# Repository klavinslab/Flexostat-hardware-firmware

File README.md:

# The project has moved to it's own [github page](https://github.com/flexostat ).

Please visit https://github.com/flexostat for the latest designs.

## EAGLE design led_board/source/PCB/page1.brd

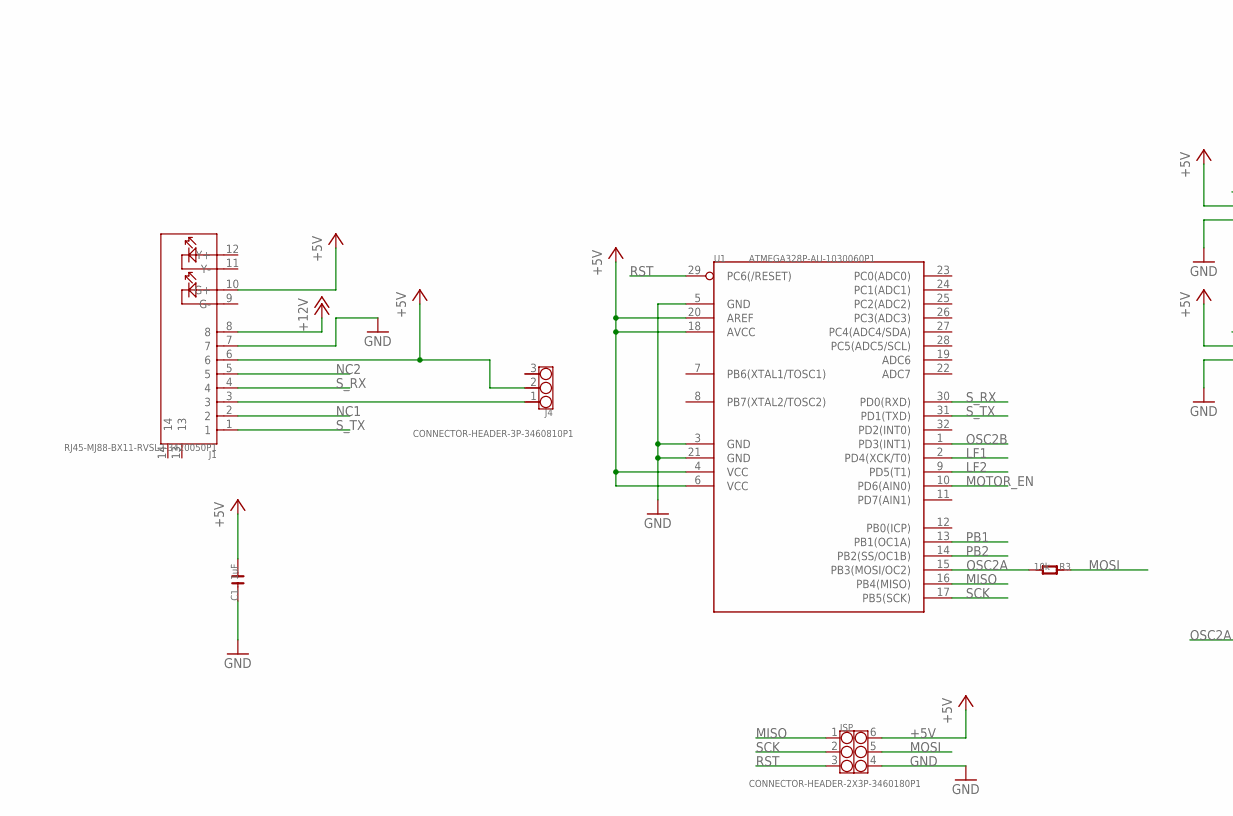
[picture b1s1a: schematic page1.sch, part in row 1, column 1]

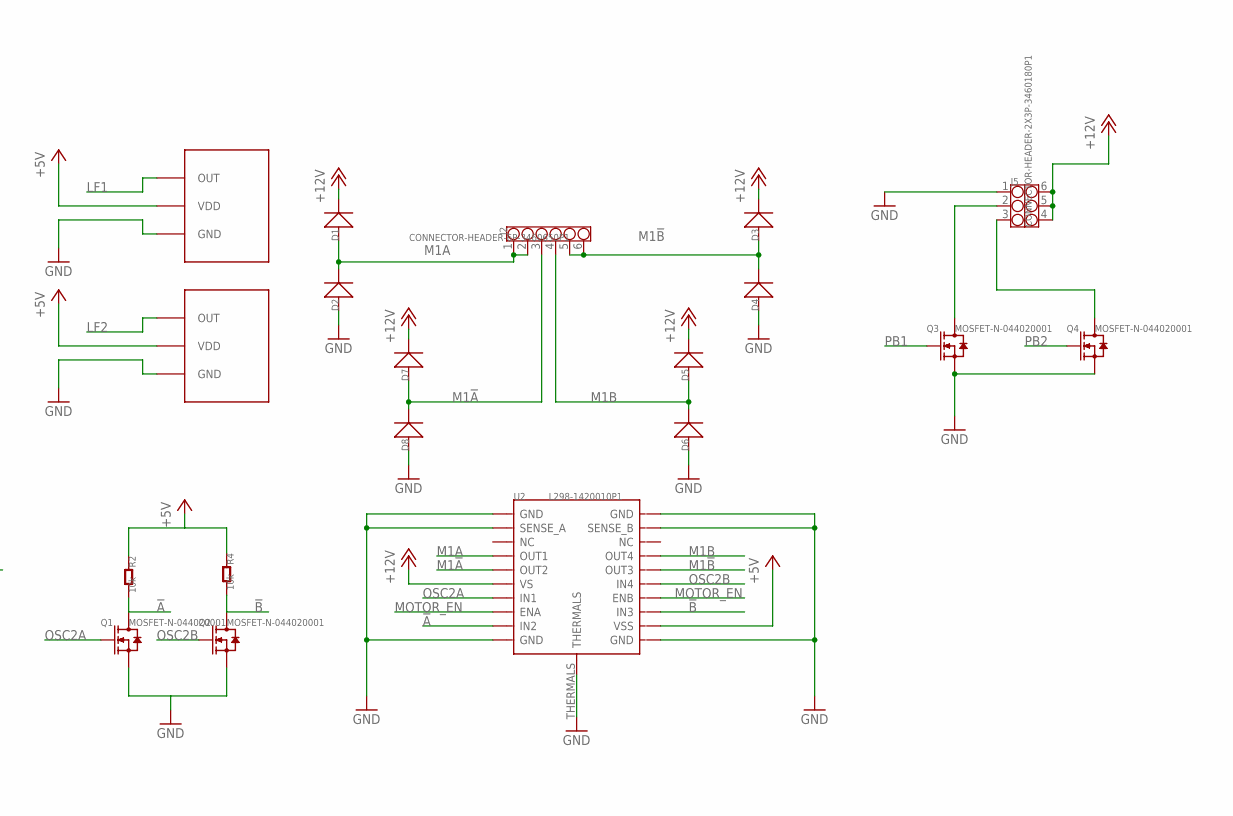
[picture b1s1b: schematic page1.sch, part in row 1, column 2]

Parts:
C1: 1uF; C0805
D1, D2, D3, D4, D5, D6, D7, D8: D-SMA; DO-214AC
ISP: CONNECTOR-HEADER-2X3P-3460180P1; 2X3P-2.54-2.54-11.6-3.0-BLACK-MALE
J1: RJ45-MJ88-BX11-RVSL2-3420050P1; RJ45-MJ88-BX11-RVSL2
J2: CONNECTOR-HEADER-6P-3460650P1; 1X6P-2.54-2.54-11.6-3.0-BLACK-MALE
J4: CONNECTOR-HEADER-3P-3460810P1; 1X3P-2.54-2.54-11.6-3.0-BLACK-MALE
J5: CONNECTOR-HEADER-2X3P-3460180P1; 2X3P-2.54-2.54-11.6-3.0-BLACK-MALE
Q1, Q2, Q3, Q4: MOSFET-N-044020001; SOT23
R2, R3, R4: 10k; R0603
U1: ATMEGA328P-AU-1030060P1; TQFP32
U2: L298-1420010P1; POWERSO-20
U$5, U$6: TSL235; TSL235R-2MM-S

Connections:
!A: Q1.3 (D), R2.2, U2.9 (IN2)
!B: Q2.3 (D), R4.2, U2.13 (IN3)
+5V: C1.2, ISP.6, J1.6, J1.10 (G+), J4.2, R2.1, R4.1, U1.4 (VCC), U1.6 (VCC), U1.18 (AVCC), U1.20 (AREF), U2.12 (VSS), U$5.P$2 (VDD), U$6.P$2 (VDD)
+12V: D1.2 (-), D3.2 (-), D5.2 (-), D7.2 (-), J1.8, J5.4, J5.5, J5.6, U2.6 (VS)
GND: C1.1, D2.1 (+), D4.1 (+), D6.1 (+), D8.1 (+), ISP.4, J1.7, J5.1, Q1.2 (S), Q2.2 (S), Q3.2 (S), Q4.2 (S), U1.3 (GND), U1.5 (GND), U1.21 (GND), U2.1 (GND), U2.2 (SENSE_A), U2.10 (GND), U2.11 (GND), U2.19 (SENSE_B), U2.20 (GND), U2.THERMALS, U$5.P$1 (GND), U$6.P$1 (GND)
LF1: U1.2 (PD4(XCK/T0)), U$5.P$3 (OUT)
LF2: U1.9 (PD5(T1)), U$6.P$3 (OUT)
M1!A: D7.1 (+), D8.2 (-), J2.3, U2.5 (OUT2)
M1!B: D3.1 (+), D4.2 (-), J2.5, J2.6, U2.16 (OUT3)
M1A: D1.1 (+), D2.2 (-), J2.1, J2.2, U2.4 (OUT1)
M1B: D5.1 (+), D6.2 (-), J2.4, U2.17 (OUT4)
MISO: ISP.1, U1.16 (PB4(MISO))
MOSI: ISP.5, R3.1
MOTOR_EN: U1.10 (PD6(AIN0)), U2.8 (ENA), U2.14 (ENB)
unnamed: J1.3, J4.1
unnamed: J5.3, Q4.3 (D)
unnamed: J5.2, Q3.3 (D)
NC1: J1.2
NC2: J1.5
OSC2A: Q1.1 (G), R3.2, U1.15 (PB3(MOSI/OC2)), U2.7 (IN1)
OSC2B: Q2.1 (G), U1.1 (PD3(INT1)), U2.15 (IN4)
PB1: Q3.1 (G), U1.13 (PB1(OC1A))
PB2: Q4.1 (G), U1.14 (PB2(SS/OC1B))
RST: ISP.3, U1.29 (PC6(/RESET))
SCK: ISP.2, U1.17 (PB5(SCK))
S_RX: J1.4, U1.30 (PD0(RXD))
S_TX: J1.1, U1.31 (PD1(TXD))

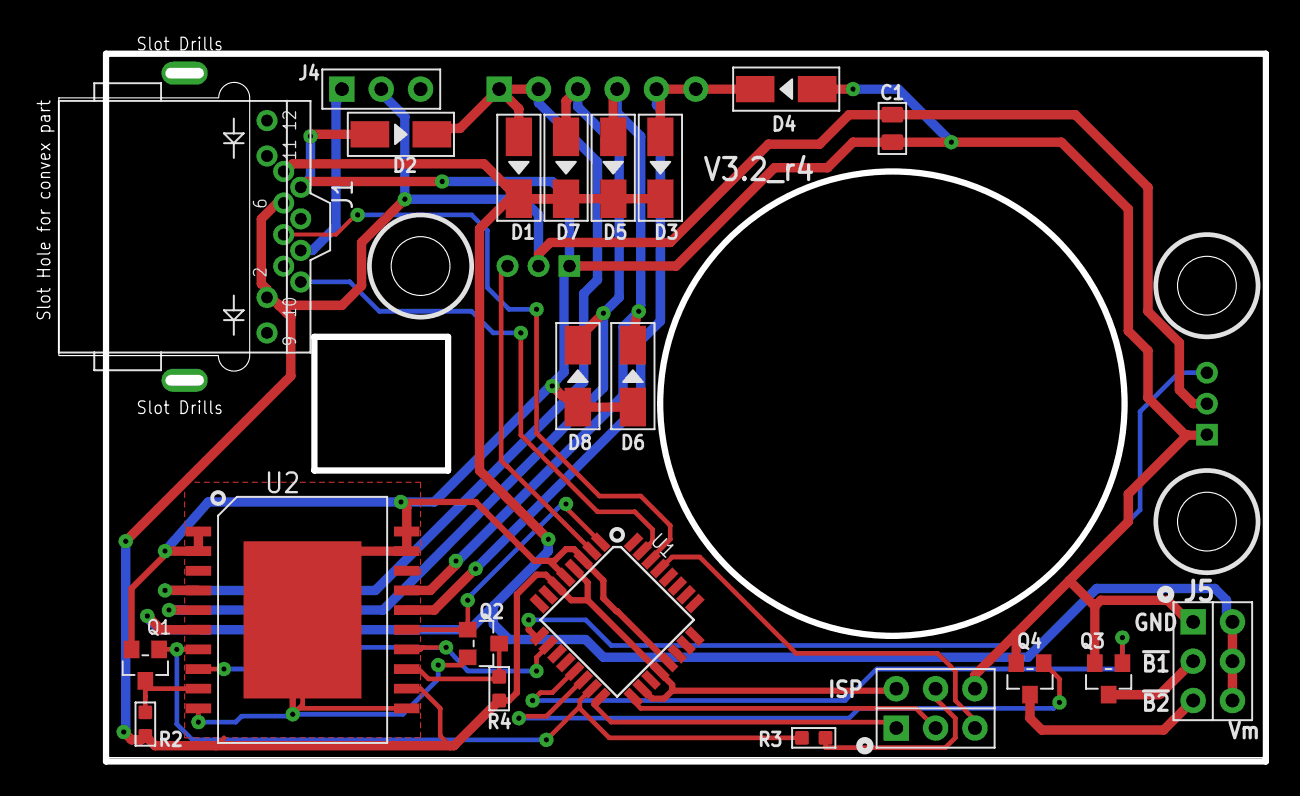
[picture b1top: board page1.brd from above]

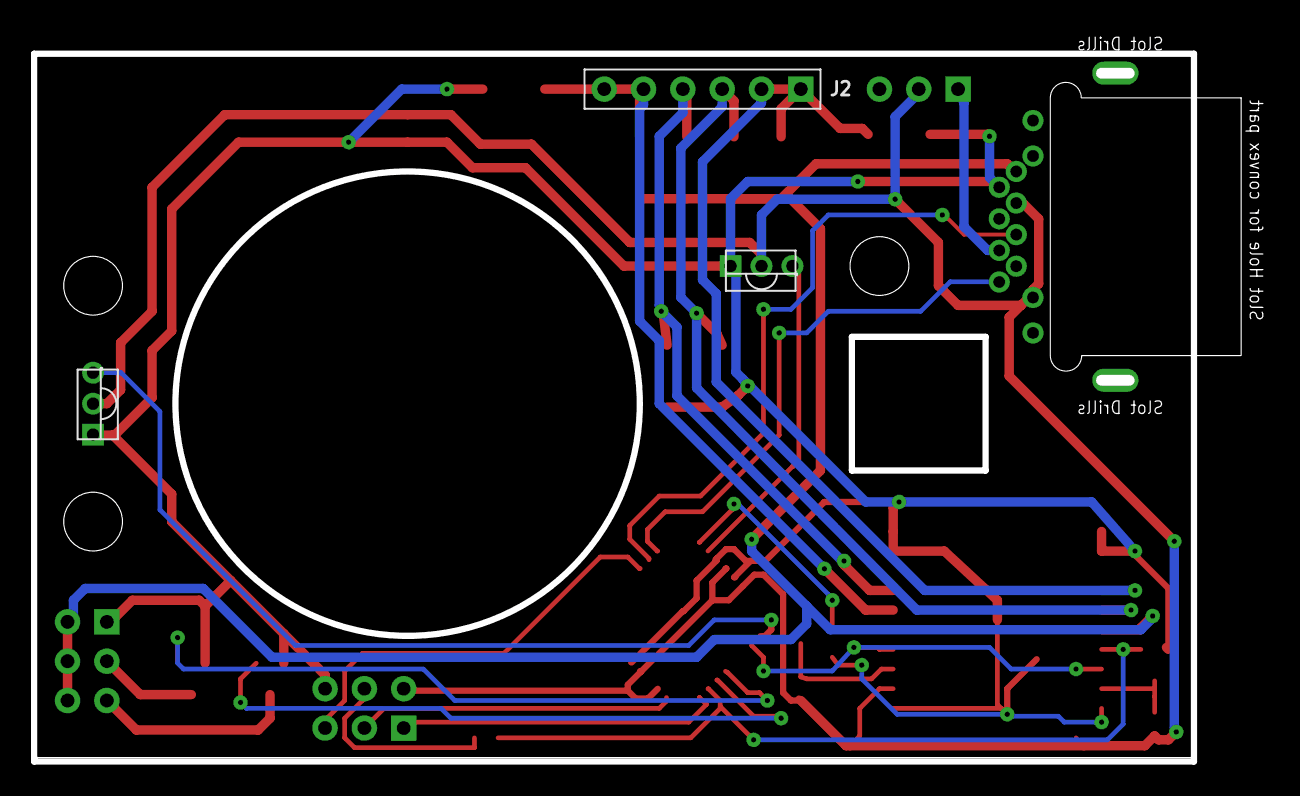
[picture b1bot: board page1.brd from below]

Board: 4 copper layers, 79.3 x 46.7 mm, 25 parts (3 on the bottom side), 25 nets.

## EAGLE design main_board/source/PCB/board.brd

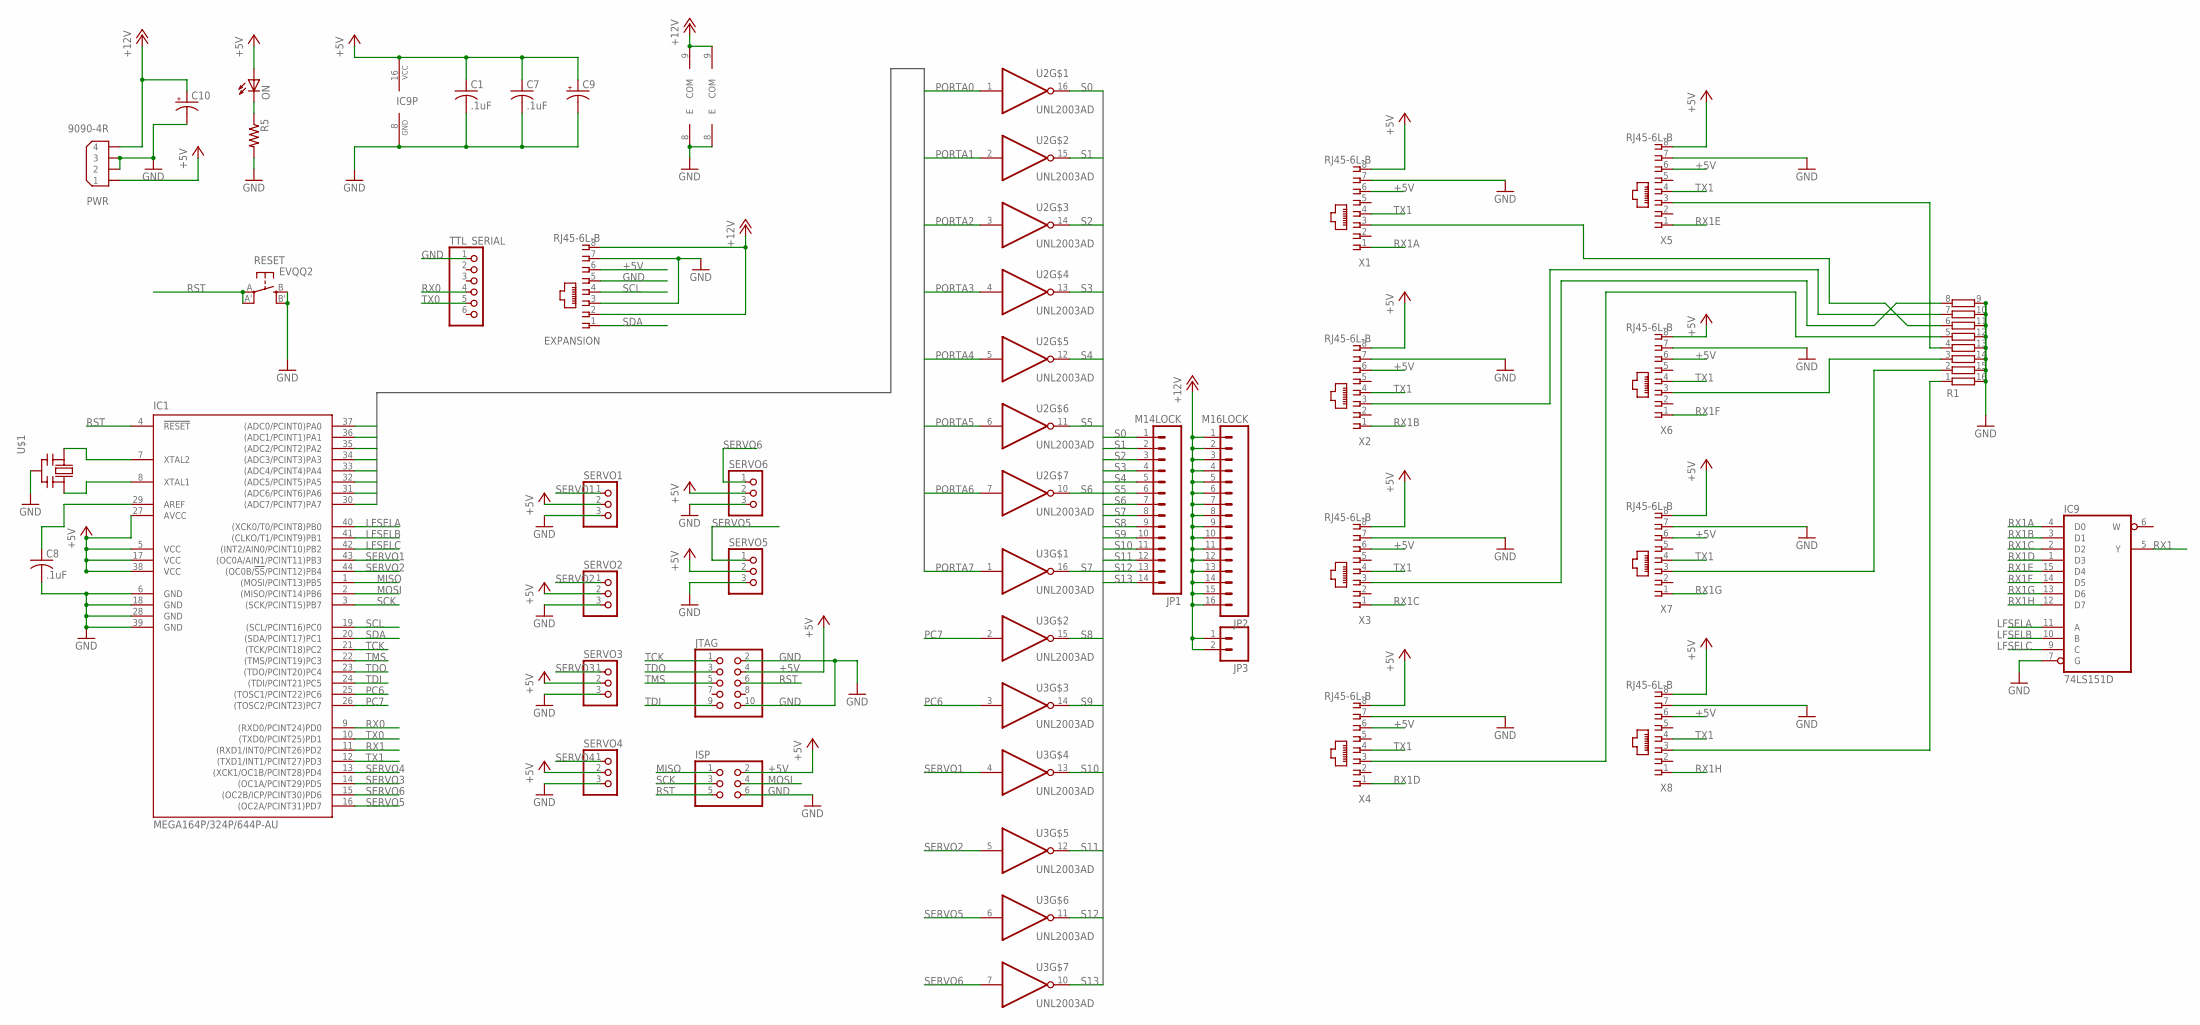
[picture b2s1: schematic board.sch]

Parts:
C1, C7, C8: .1uF; C0805
C9, C10: CPOL-USE2.5-7; E2,5-7
EXPANSION: RJ45-6L-B; RJ45-NO-SHIELD
IC1: MEGA164P/324P/644P-AU; TQFP44
IC9: 74LS151D; SO16
ISP: PINHD-2X3; 2X03
JP1: M14LOCK; 1X14_LOCK
JP2: M16LOCK; 1X16_LOCK
JP3: M02PTH; 1X02
JTAG: PINHD-2X5; 2X05
ON: LEDCHIPLED_0805; CHIPLED_0805
PWR: 9090-4R
R1: 2NBS16-8; SO16
R5: R-US_R0805; R0805
RESET: EVQQ2; EVQ-Q2
SERVO1, SERVO2, SERVO3, SERVO4, SERVO5, SERVO6: PINHD-1X3; 1X03
TTL_SERIAL: PINHD-1X6; 1X06
U2, U3: UNL2003AD; SO16
U$1: CERMOSCILL-CSTCRG; CSTCR-G
X1, X2, X3, X4, X5, X6, X7, X8: RJ45-6L-B; RJ45-NO-SHIELD

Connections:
+5V: C1.1, C7.1, C9.+, EXPANSION.6, IC1.5 (VCC), IC1.17 (VCC), IC1.27 (AVCC), IC1.38 (VCC), IC9.16 (VCC), ISP.2, JTAG.4, ON.A, PWR.1, SERVO1.2, SERVO2.2, SERVO3.2, SERVO4.2, SERVO5.2, SERVO6.2, X1.6, X1.8, X2.6, X2.8, X3.6, X3.8, X4.6, X4.8, X5.6, X5.8, X6.6, X6.8, X7.6, X7.8, X8.6, X8.8
+12V: C10.+, EXPANSION.2, EXPANSION.8, JP2.1, JP2.2, JP2.3, JP2.4, JP2.5, JP2.6, JP2.7, JP2.8, JP2.9, JP2.10, JP2.11, JP2.12, JP2.13, JP2.14, JP2.15, JP2.16, JP3.1, JP3.2, PWR.4, U2.9 (COM), U3.9 (COM)
GND: C1.2, C7.2, C8.2, C9.-, C10.-, EXPANSION.3, EXPANSION.5, EXPANSION.7, IC1.6 (GND), IC1.18 (GND), IC1.28 (GND), IC1.39 (GND), IC9.7 (G), IC9.8 (GND), ISP.6, JTAG.2, JTAG.10, PWR.2, PWR.3, R1.9, R1.10, R1.11, R1.12, R1.13, R1.14, R1.15, R1.16, R5.2, RESET.B (S), RESET.B' (S1), SERVO1.3, SERVO2.3, SERVO3.3, SERVO4.3, SERVO5.3, SERVO6.3, TTL_SERIAL.1, U2.8 (E), U3.8 (E), U$1.2 (GND), X1.7, X2.7, X3.7, X4.7, X5.7, X6.7, X7.7, X8.7
LFSELA: IC1.40 ((XCK0/T0/PCINT8)PB0), IC9.11 (A)
LFSELB: IC1.41 ((CLKO/T1/PCINT9)PB1), IC9.10 (B)
LFSELC: IC1.42 ((INT2/AIN0/PCINT10)PB2), IC9.9 (C)
MISO: IC1.1 ((MOSI/PCINT13)PB5), ISP.1
MOSI: IC1.2 ((MISO/PCINT14)PB6), ISP.4
unnamed: IC1.7 (XTAL2), U$1.1 (IN)
unnamed: IC1.8 (XTAL1), U$1.3 (OUT)
unnamed: R1.1, X8.3
unnamed: R1.6, X1.3
unnamed: R1.7, X2.3
unnamed: R1.8, X3.3
unnamed: R1.5, X4.3
unnamed: R1.4, X5.3
unnamed: R1.3, X6.3
unnamed: R1.2, X7.3
unnamed: C8.1, IC1.29 (AREF)
unnamed: ON.C, R5.1
PC6: IC1.25 ((TOSC1/PCINT22)PC6), U3.3 (I)
PC7: IC1.26 ((TOSC2/PCINT23)PC7), U3.2 (I)
PORTA0: IC1.37 ((ADC0/PCINT0)PA0), U2.1 (I)
PORTA1: IC1.36 ((ADC1/PCINT1)PA1), U2.2 (I)
PORTA2: IC1.35 ((ADC2/PCINT2)PA2), U2.3 (I)
PORTA3: IC1.34 ((ADC3/PCINT3)PA3), U2.4 (I)
PORTA4: IC1.33 ((ADC4/PCINT4)PA4), U2.5 (I)
PORTA5: IC1.32 ((ADC5/PCINT5)PA5), U2.6 (I)
PORTA6: IC1.31 ((ADC6/PCINT6)PA6), U2.7 (I)
PORTA7: IC1.30 ((ADC7/PCINT7)PA7), U3.1 (I)
RST: IC1.4 (!RESET), ISP.5, JTAG.6, RESET.A, RESET.A' (P1)
RX0: IC1.9 ((RXD0/PCINT24)PD0), TTL_SERIAL.4
RX1: IC1.11 ((RXD1/INT0/PCINT26)PD2), IC9.5 (Y)
RX1A: IC9.4 (D0), X1.1
RX1B: IC9.3 (D1), X2.1
RX1C: IC9.2 (D2), X3.1
RX1D: IC9.1 (D3), X4.1
RX1E: IC9.15 (D4), X5.1
RX1F: IC9.14 (D5), X6.1
RX1G: IC9.13 (D6), X7.1
RX1H: IC9.12 (D7), X8.1
S0: JP1.1, U2.16 (O)
S1: JP1.2, U2.15 (O)
S2: JP1.3, U2.14 (O)
S3: JP1.4, U2.13 (O)
S4: JP1.5, U2.12 (O)
S5: JP1.6, U2.11 (O)
S6: JP1.7, U2.10 (O)
S7: JP1.8, U3.16 (O)
S8: JP1.9, U3.15 (O)
S9: JP1.10, U3.14 (O)
S10: JP1.11, U3.13 (O)
S11: JP1.12, U3.12 (O)
S12: JP1.13, U3.11 (O)
S13: JP1.14, U3.10 (O)
SCK: IC1.3 ((SCK/PCINT15)PB7), ISP.3
SCL: EXPANSION.4, IC1.19 ((SCL/PCINT16)PC0)
SDA: EXPANSION.1, IC1.20 ((SDA/PCINT17)PC1)
SERVO1: IC1.43 ((OC0A/AIN1/PCINT11)PB3), SERVO1.1, U3.4 (I)
SERVO2: IC1.44 ((OC0B/!SS!/PCINT12)PB4), SERVO2.1, U3.5 (I)
SERVO3: IC1.14 ((OC1A/PCINT29)PD5), SERVO3.1
SERVO4: IC1.13 ((XCK1/OC1B/PCINT28)PD4), SERVO4.1
SERVO5: IC1.16 ((OC2A/PCINT31)PD7), SERVO5.1, U3.6 (I)
SERVO6: IC1.15 ((OC2B/ICP/PCINT30)PD6), SERVO6.1, U3.7 (I)
TCK: IC1.21 ((TCK/PCINT18)PC2), JTAG.1
TDI: IC1.24 ((TDI/PCINT21)PC5), JTAG.9
TDO: IC1.23 ((TDO/PCINT20)PC4), JTAG.3
TMS: IC1.22 ((TMS/PCINT19)PC3), JTAG.5
TX0: IC1.10 ((TXD0/PCINT25)PD1), TTL_SERIAL.5
TX1: IC1.12 ((TXD1/INT1/PCINT27)PD3), X1.4, X2.4, X3.4, X4.4, X5.4, X6.4, X7.4, X8.4

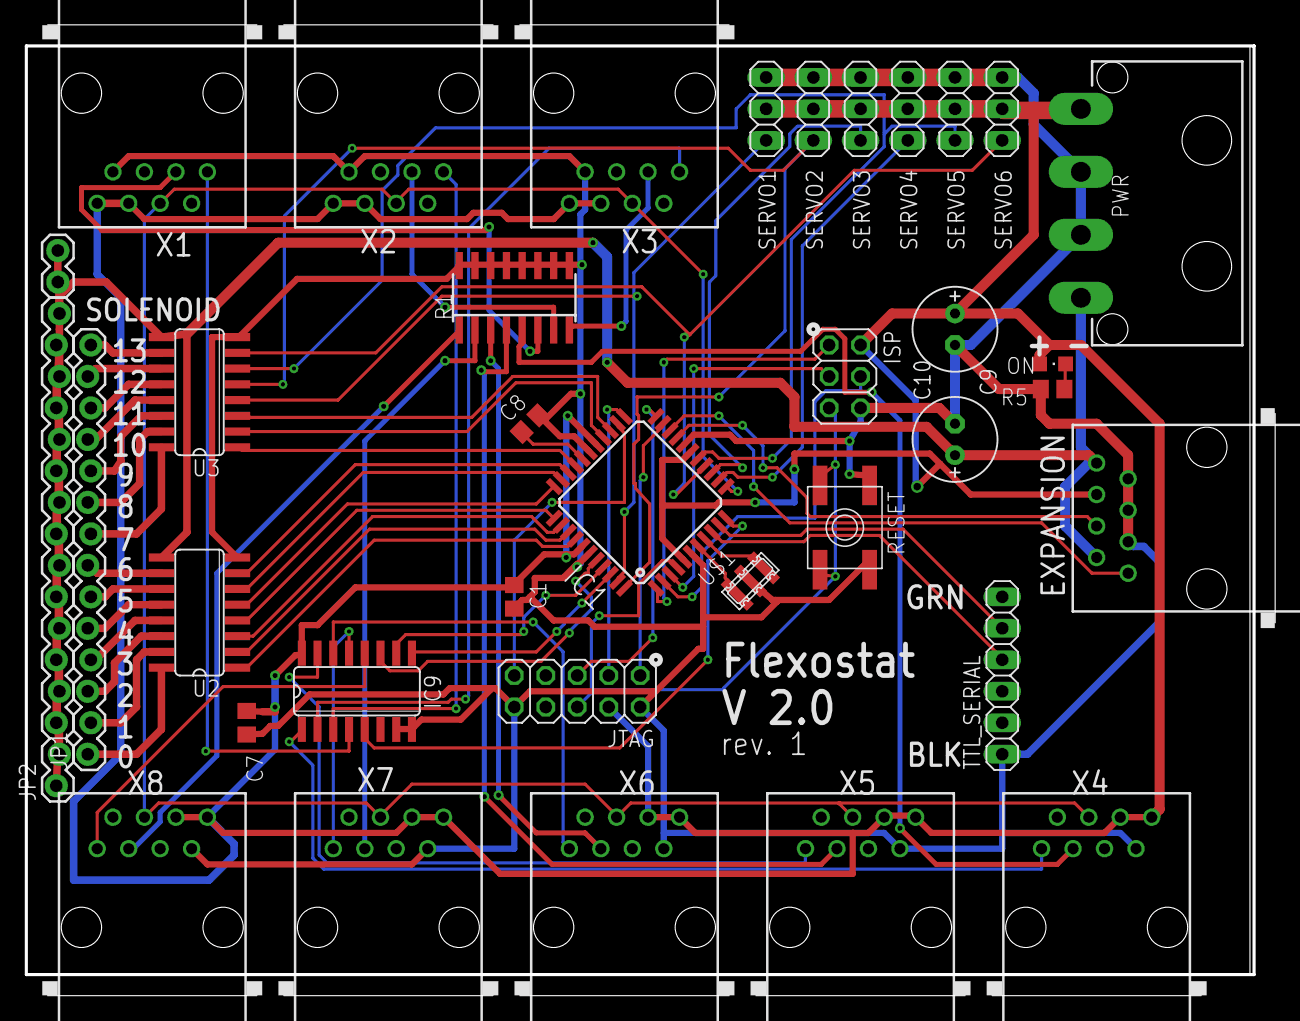
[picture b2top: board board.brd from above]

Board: 2 copper layers, 100.6 x 78.1 mm, 36 parts (0 on the bottom side), 70 nets.

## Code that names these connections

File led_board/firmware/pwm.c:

/*
 * pwm.c
 *
 * Created: 8/2/2011 3:10:29 PM
 *  Author: soslab
 */ 
#include "pwm.h"
#include <avr/io.h>
#include <avr/interrupt.h>

volatile uint16_t epocht;

//setup stir motor PWM
//TODO: convert this to work with timer2
void pwm_init() {
	/******STIR INIT*******/
#if defined(__AVR_ATmega328P__) || defined(__AVR_ATmega328__)
  DDRB |= 0x08 //PB3:OSC2A output 
  DDRD |= 0x08 //PD3:OSC2B output
#elif defined(__AVR_ATmega164A__) || defined(__AVR_ATmega164P__)
	DDRD |= 0x80 | 0x40;	
#else
#error "UNSUPPORTED arcitecture.  Cannot continue"
#endif
	
	//CTC mode, toggle on compare match A, B
	TCCR2A = 0x02 | 0x40 | 0x10;
	//cksel /1024, 
	TCCR2B = 0x07;
	
	//toggle on couter top and half counter top to create 90deg phase
	OCR2A = COUNTER_TOP;
	OCR2B = COUNTER_TOP/2;
	
	TIMSK2 = 1<<OCIE2A; //Enable match A interrupt.
	epocht = 0;
	
}

//one epoch is 2/STIR_SPEED seconds
ISR (TIMER2_COMPA_vect) {
	epocht++;	
}

//this is a low res estimate of current time
// it is roughly 2/STIR_SPEED of a second accurate.
// ie for STIR_SPEED=400 it is accurate to +/- 5 millis
uint32_t millis() {
	//note last set of () kills percision, but right now it divides evenly.
	return (epocht*(2000L/STIR_SPEED));
}

uint16_t epoch() {
	return epocht;
}

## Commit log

2012-11-03 First commit of turbidostat 1.0 hardware and firmware files
2012-11-03 added LICENSE.TXT
2013-03-06 added firmware code
2013-08-05 updated chamber. raised laser height to avoid catching stirbar. reworked laser holder, should be a lot more accurate and secure. version number 7.
2013-08-06 added stl files
2014-01-10 bring uptodate.
    not sure how this file is different. I forgot what change this is. may
    need to revert if this is a mistake.
2014-01-11 tweaked file names to remove spaces
2014-01-11 added step and stl versions of all 3d parts
    also added different sized pinch valves clips.
2014-03-11 small updates and improvements
2014-03-18 added eagle files for LED board. version 3.1
2014-03-18 updated to version 3.2 of led PCB
2014-03-19 added BOM file for ordering LED board from seeed studio preassembled
2014-03-19 first test port to new ATMEGA part. should also compile for old 164 part
2014-03-19 added error check at complie time
2014-04-04 added support for LED board version 3.2
2014-04-04 Updated PCB design for ledboard 3.2r1
2014-04-04 updated chamber design to accomidate the new motor
2014-04-21 updated delrin parts
2014-05-13 reorg directory structure
2014-05-13 more file reorg
2014-05-13 updated c code to reflect new boards. included hex file
2014-05-13 updated directory structure and added binaries
2014-05-13 more directory reorg
2014-05-13 last directory rework
2014-05-13 updated readme to reflect new directory struture
2014-07-31 clairfication
2014-08-07 update to syringe pump. More robust with black plastic. easier to assemble
2014-08-07 LED board update rev3. Vs and Vss corrected
2014-08-08 added git ignore
2014-08-08 updated gitignore
2014-08-13 code update for mainboard v2.0
2014-08-29 updated software license to BSD
2014-08-29 updated software license to BSD (added actual file, oops)
2014-11-18 made a 2-part stopper mold for easy removal
2014-11-18 added a full chamber assembly for printing on SLS printers
2014-11-18 fixed whitespace
2014-11-18 Added SPV pulse functionality for syphoning media.--ONLY COMPATIBLE WITH NEWEST MAINBOARD LABELED 'FLEXOSTAT V2.0'--
2014-11-18 udptade to FLEXOSTAT V2.0
2014-11-18 fixed overlay layer. SPV numbers now line up with pins
2014-12-18 tightened tolerances
2014-12-19 millis now counts the full range of uint16_t.
2014-12-19 added git ignore to ignore compiled code and project files
2014-12-19 tabs->spaces. And added PV pulse support on B1
2014-12-19 added syphonstat binary
2014-12-19 now pulls enable pin high for stirring on newest board rev
2015-04-14 small firmware but where chamber 8 wouldn't close under some circumstances
2015-04-14 updated binaries. added production file
2015-04-14 minor chamber update
2015-04-14 small changes
2015-04-14 updated syringe body holder. top no longer needed!
2015-04-14 top not needed
2015-04-17 basic i2c support
2015-04-17 i2c PV support
2015-08-12 added control over stirrer driver OE
2015-08-12 updated bom file for seeed's new format
2015-08-21 experimental new designs
2015-08-22 switched to openSCAD. These designs should work!
2015-08-22 experimental pinchvalve
2015-08-25 new stopper mold. 3 parts.
2015-08-28 fixed bom to align with seeed's new partnumber
2015-08-29 working for 25mm tubes, printing at .3mm layers
2015-08-30 holes go all the way through
2015-09-08 magnet holder
2015-09-08 soldering jig
2015-09-24 parameter updates (working)
2015-09-24 recessed screws
2015-09-30 fixed unit conversion 24.5->25.4
2015-09-30 update stls
2015-09-30 updated mount plate width
2015-09-30 fixed partnumber changed by seeed
